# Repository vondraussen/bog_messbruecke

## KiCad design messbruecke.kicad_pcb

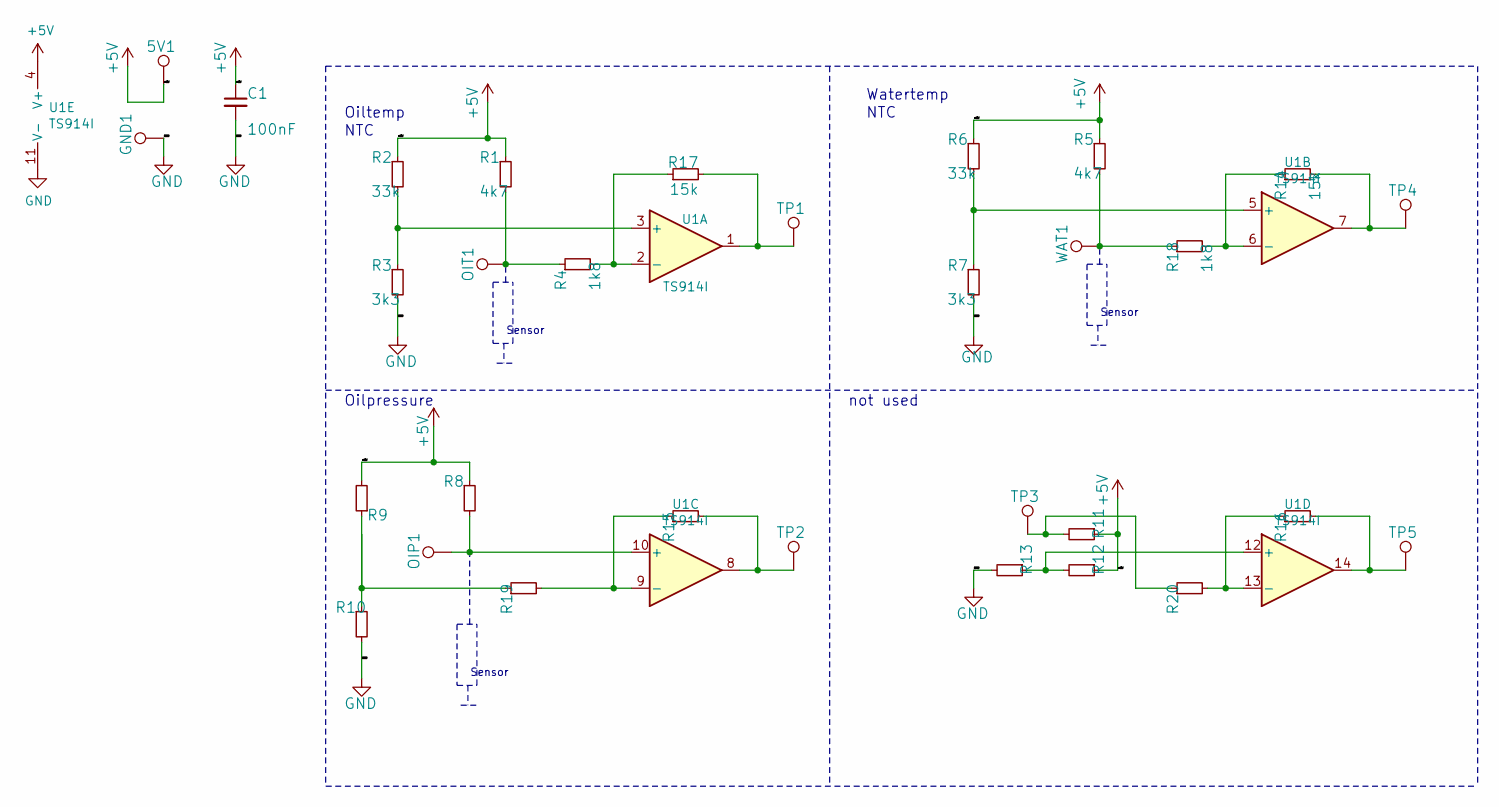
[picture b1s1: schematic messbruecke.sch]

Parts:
5V1: TPTP15SQ; TestPoint_Pad_1.5x1.5mm
C1: 100nF; C_0805_2012Metric
GND1: TPTP15SQ; TestPoint_Pad_1.5x1.5mm
OIP1: TPTP15SQ; TestPoint_Pad_1.5x1.5mm
OIT1: TPTP15SQ; TestPoint_Pad_1.5x1.5mm
R1, R5: 4k7; R_0805_2012Metric
R2, R6: 33k; R_0805_2012Metric
R3, R7: 3k3; R_0805_2012Metric
R4, R18: 1k8; R_0805_2012Metric
R8, R9, R10, R11, R12, R13, R15, R16, R19, R20: R-EU_R0805W; R_0805_2012Metric
R14, R17: 15k; R_0805_2012Metric
TP1, TP2, TP3, TP4, TP5: TPTP15SQ; TestPoint_Pad_1.5x1.5mm
U1: TS914I; SOIC-14_3.9x8.7mm_P1.27mm
WAT1: TPTP15SQ; TestPoint_Pad_1.5x1.5mm

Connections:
+5V: 5V1.1, C1.1, R1.1, R2.1, R5.1, R6.1, R8.1, R9.2, R11.1, R12.1, U1.4 (V+)
GND: C1.2, GND1.1, R3.2, R7.2, R10.2, R13.2, U1.11 (V-)
unnamed: OIP1.1, R8.2, U1.10 (+)
unnamed: OIT1.1, R1.2, R4.1
unnamed: R2.2, R3.1, U1.3 (+)
unnamed: R6.2, R7.1, U1.5 (+)
unnamed: R9.1, R10.1, R19.1
unnamed: R11.2, R20.1, TP3.1
unnamed: R12.2, R13.1, U1.12 (+)
unnamed: R14.1, R18.2, U1.6 (-)
unnamed: R14.2, TP4.1, U1.7
unnamed: R15.1, R19.2, U1.9 (-)
unnamed: R15.2, TP2.1, U1.8
unnamed: R16.1, R20.2, U1.13 (-)
unnamed: R16.2, TP5.1, U1.14
unnamed: R4.2, R17.1, U1.2 (-)
unnamed: R17.2, TP1.1, U1.1
unnamed: R5.2, R18.1, WAT1.1

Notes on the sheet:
Oiltemp
Oilpressure
Watertemp
not used
NTC
Sensor

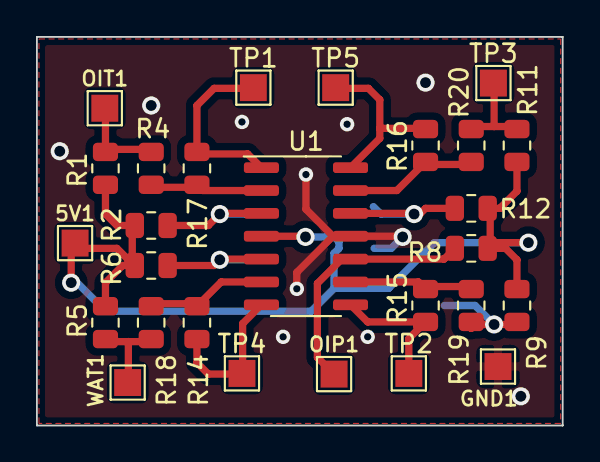
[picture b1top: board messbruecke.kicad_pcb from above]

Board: 2 copper layers, 29.2 x 21.6 mm, 32 parts (0 on the bottom side), 18 nets.

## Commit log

2021-02-27 converted from eagle
